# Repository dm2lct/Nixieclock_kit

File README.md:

Better version of my nixie clock. 
=====

Feel free to build your own nixie clock from it.

The firmware can be found at https://codeberg.org/paul/nixie_clock

The documentation and assembly instructions are on https://wiki.turmlabor.de/index.php?title=Nixie_Uhr_Bausatz_2.1 (currently only in german, sorry!)

Features:
  - IN14 nixie tubes but you can adapt many other nixie tubes, but some of them would not fit nicely in the board
  - ESP12e controller so you can make IoT with it and build your own botnet for world domination, if you have enough clocks.
    But mainly the wifi is used to get the time from a ntp-server and for controlling the clock with MQTT
  - DS3231 RTC for everyone who does not like IoT and does also not want to be enslaved from AI
  - WS2812B under each nixie tube to make them look more fancy
  - runs from a simple USB charger, although it uses a mini-usb B socket, which is better to solder, so you need a mini-usb cable
  - you can program the controller with your Arduino IDE over USB
  - optimized nixie power supply. Now the entire clock ownly draws about 450mA from the power supply
  - cleaned up the schematic a little: Simpler protection circuit

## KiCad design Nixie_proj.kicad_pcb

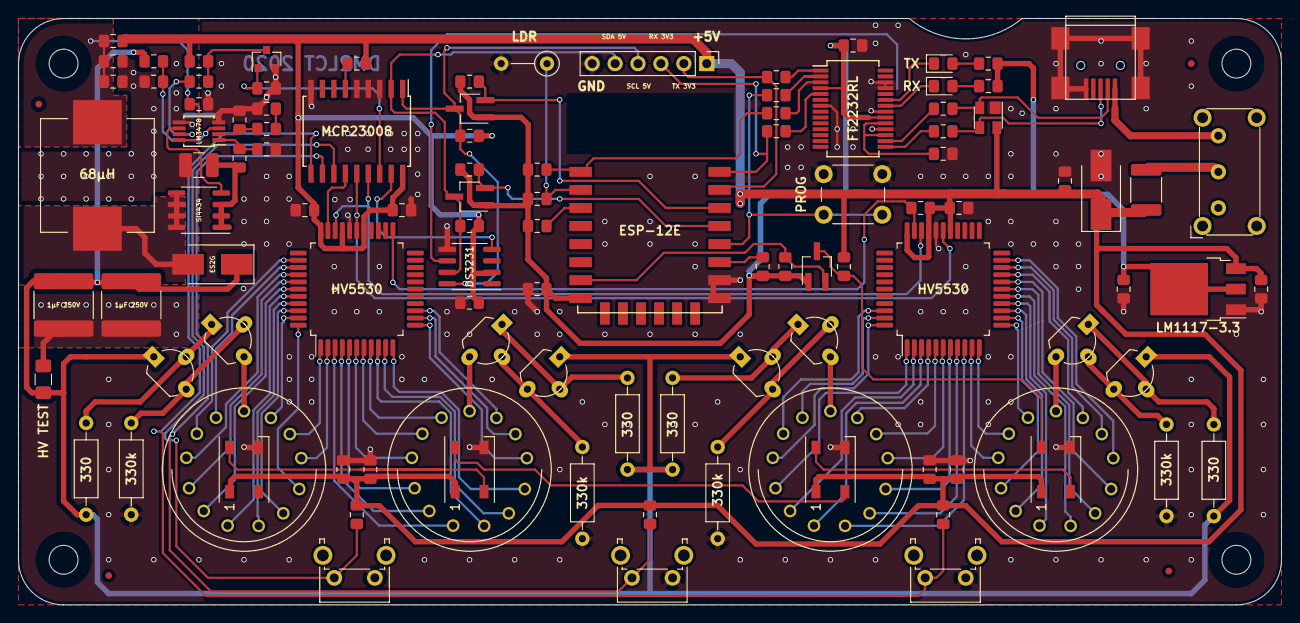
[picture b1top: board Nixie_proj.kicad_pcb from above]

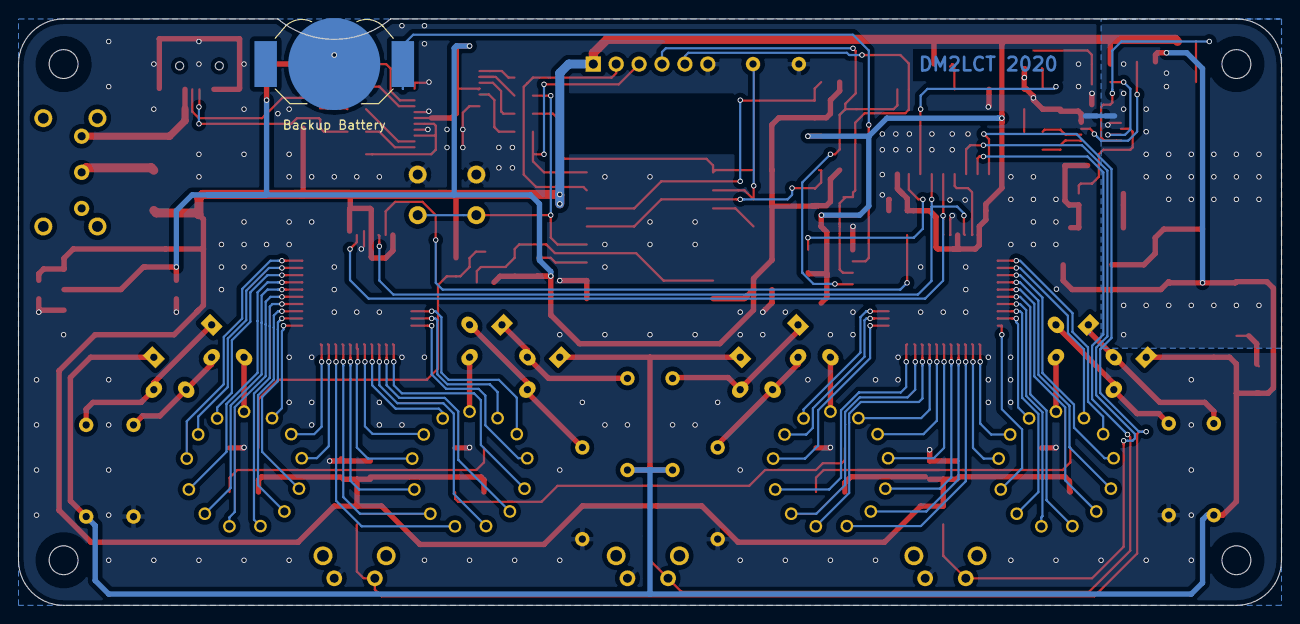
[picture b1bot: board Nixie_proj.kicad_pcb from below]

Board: 2 copper layers, 140.0 x 65.0 mm, 117 parts (2 on the bottom side), 117 nets.

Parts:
1µF 250V, 1µF 250V#2: 1u; C_2225_5664Metric_Pad1.80x6.60mm_HandSolder
68µH: INDUCTOR; L_Wuerth_WE-PD-Typ-LS_Handsoldering
330, 330#2, 330#3, 330#4: 330; R_Axial_DIN0207_L6.3mm_D2.5mm_P10.16mm_Horizontal
330k, 330k#2, 330k#3, 330k#4: 330k; R_Axial_DIN0207_L6.3mm_D2.5mm_P10.16mm_Horizontal
Backup Battery: Battery_Cell; BatteryHolder_LINX_BAT-HLD-012-SMT
C1, C5, C6, C8, C14, C16, C17, C18, C19, C20, C21, C22, C23, C201: 2.2u; C_0805_2012Metric_Pad1.15x1.40mm_HandSolder
C2, C3, C4: 22u; C_0805_2012Metric_Pad1.15x1.40mm_HandSolder
C7: 150p; C_0805_2012Metric_Pad1.15x1.40mm_HandSolder
C9: 1n; C_0805_2012Metric_Pad1.15x1.40mm_HandSolder
C305: 3n3; C_0805_2012Metric_Pad1.15x1.40mm_HandSolder
D1: P6SMB6,8A; D_SMB_Handsoldering
D2: PRTR5V0U2X; SOT-143
DS3231: DS3231MZ; SOIC-8_3.9x4.9mm_P1.27mm
ES2G: ES2G/SMB; D_SMB_Handsoldering
ESP-12E: ESP-12E; ESP-12E_SMD
F1: 2,2A; Fuse_1812_4532Metric_Pad1.30x3.40mm_HandSolder
FID1, FID2, FID3, FID4: Fiducial; Fiducial_0.75mm_Mask1.5mm
FT2232RL: FT232RL; SSOP-28_5.3x10.2mm_P0.65mm
H1, H2, H3: MountingHole; MountingHole_3.2mm_M3_DIN965
H4: eMountingHole; MountingHole_3.2mm_M3_DIN965
HV5530, HV5530#2: HV5530; MQFP-44_10x10mm_P0.8mm
HV TEST: TEST; R_1206_3216Metric_Pad1.42x1.75mm_HandSolder
J1: Conn_01x06_Male; PinHeader_1x06_P2.54mm_Vertical
L4: Ferrite_Bead; L_0805_2012Metric_Pad1.15x1.40mm_HandSolder
LDR: R_PHOTO; R_Axial_DIN0207_L6.3mm_D2.5mm_P5.08mm_Vertical
LED401, LED402, LED403, LED404: WS2812B; LED_WS2812B_PLCC4_5.0x5.0mm_P3.2mm
LM1117-3.3: LM1117-3.3; TO-252-3_TabPin2
LM3478: LM3478; MSOP-8_3x3mm_P0.65mm
MCP23008: MCP23008; SOIC-18W_7.5x11.6mm_P1.27mm
NT1: Net-Tie_2; NetTie-2_SMD_Pad0.5mm
P301: USB Buchse; USB_Mini-B
PROG: SW_Push; SW_PUSH_6mm_H4.3mm
Q2: BSS138; SOT-23
Q202, Q203, Q204, Q205, Q206, Q207, Q208, Q209: MPSA92; TO-92_Molded_Wide_Oval
Q401, Q403, Q404: BSS138; SOT-23W_Handsoldering
R1: 68k1; R_0805_2012Metric_Pad1.15x1.40mm_HandSolder
R2, R3, R206, R310, R401, R402, R403, R410, R411, R412, R413, R414, R416, R417, R418, R419, R420, R421: 10k; R_0805_2012Metric_Pad1.15x1.40mm_HandSolder
R4: 51k1; R_0805_2012Metric_Pad1.15x1.40mm_HandSolder
R5: 1k; R_0805_2012Metric_Pad1.15x1.40mm_HandSolder
R308: 1M5; R_0805_2012Metric_Pad1.15x1.40mm_HandSolder
R404, R405, R406, R407: 10R; R_0805_2012Metric_Pad1.15x1.40mm_HandSolder
R408, R409: 120; R_0805_2012Metric_Pad1.15x1.40mm_HandSolder
RSENSE301: 0R050; R_1210_3225Metric_Pad1.42x2.65mm_HandSolder
RX: GRÜN; LED_0805_2012Metric_Pad1.15x1.40mm_HandSolder
SI4434: SI4434; SOIC-8_3.9x4.9mm_P1.27mm
SW1: EG1224; SW_E-Switch_EG1224_SPDT_Angled
SW402: Rechts; SW_Tactile_SPST_Angled_PTS645Vx39-2LFS
SW403: Mitte; SW_Tactile_SPST_Angled_PTS645Vx39-2LFS
SW404: Links; SW_Tactile_SPST_Angled_PTS645Vx39-2LFS
TBE201, TBE202, TBE203, TBE204: IN14; IN-14-mod
TX: ROT; LED_0805_2012Metric_Pad1.15x1.40mm_HandSolder
W401, W402: TEST_2P; R_0805_2012Metric_Pad1.15x1.40mm_HandSolder

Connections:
+3V3: C6.1, C18.1, C21.2, ESP-12E.8, FT2232RL.4, FT2232RL.20, LM1117-3.3.2, Q401.1, Q403.1, Q404.1, R408.1, R409.1, R410.1, R412.1, R413.1, R414.1, R418.1, R419.1, R420.1
+5V: C1.1, C2.1, C5.1, C14.1, C16.1, C17.1, C20.1, C22.1, C23.2, C201.1, D1.1, D2.4, DS3231.2, F1.1, HV5530.27, HV5530.30, HV5530.33, HV5530#2.27, HV5530#2.30, HV5530#2.33, J1.1, L4.2, LED401.1, LED402.1, LED403.1, LED404.1, LM1117-3.3.3, MCP23008.18, R3.2, R206.1, R401.2, R402.2, R403.2, R411.1, R416.1, R417.1, R421.1
/Microcontroller and clock/BTN1: MCP23008.10, R401.1, SW402.2
/Microcontroller and clock/BTN2: MCP23008.11, R402.1, SW403.2
/Microcontroller and clock/BTN3: MCP23008.12, R403.1, SW404.2
/Microcontroller and clock/HVCLOCK: HV5530.28, HV5530#2.28, MCP23008.14
/Microcontroller and clock/HVDATA: HV5530.32, MCP23008.13
/Microcontroller and clock/HVSTROBE: HV5530.31, HV5530#2.31, MCP23008.15
/Microcontroller and clock/HV_SHDN: MCP23008.16, Q2.1, R2.2
/Microcontroller and clock/RX: ESP-12E.16, J1.3, R407.1
/Microcontroller and clock/SCL_3V3: ESP-12E.14, Q403.2, R413.2
/Microcontroller and clock/SCL_5V: DS3231.8, J1.4, MCP23008.1, Q403.3, R416.2
/Microcontroller and clock/SDA_3V3: ESP-12E.13, Q404.2, R412.2
/Microcontroller and clock/SDA_5V: DS3231.7, J1.5, MCP23008.2, Q404.3, R417.2
/Microcontroller and clock/TX: ESP-12E.15, J1.2, R406.1
/Microcontroller and clock/USBD+: D2.3, P301.3, R404.2
/Microcontroller and clock/USBD-: D2.2, P301.2, R405.2
/Power Supply/Boost_Drain: 68µH.2, ES2G.2, SI4434.5, SI4434.6, SI4434.7, SI4434.8
/Power Supply/Boost_ZK: 68µH.1, C3.1, C4.1, C8.2, L4.1, LM3478.8
/Power Supply/FB: LM3478.3, R308.2, R310.1
/Power Supply/Isen: C9.2, LM3478.1, R5.2
/Power Supply/PWRGND: 1µF 250V.2, 1µF 250V#2.2, C3.2, C4.2, HV TEST.2, LM3478.5, NT1.1, R310.2, RSENSE301.2
/Tubes with drivers/A0: HV5530.2, TBE201.11
/Tubes with drivers/A1: HV5530.35, TBE201.3
/Tubes with drivers/A2: HV5530.37, TBE201.4
/Tubes with drivers/A3: HV5530.38, TBE201.5
/Tubes with drivers/A4: HV5530.39, TBE201.6
/Tubes with drivers/A5: HV5530.40, TBE201.7
/Tubes with drivers/A6: HV5530.41, TBE201.8
/Tubes with drivers/A7: HV5530.42, TBE201.9
/Tubes with drivers/A8: HV5530.44, TBE201.10
/Tubes with drivers/A9: HV5530.1, TBE201.12
/Tubes with drivers/AC1: HV5530.36, TBE201.2
/Tubes with drivers/AC2: HV5530.43, TBE201.13
/Tubes with drivers/B0: HV5530.13, TBE202.12
/Tubes with drivers/B1: HV5530.5, TBE202.5
/Tubes with drivers/B2: HV5530.6, TBE202.4
/Tubes with drivers/B3: HV5530.7, TBE202.3
/Tubes with drivers/B4: HV5530.4, TBE202.6
/Tubes with drivers/B5: HV5530.3, TBE202.7
/Tubes with drivers/B6: HV5530.9, TBE202.8
/Tubes with drivers/B7: HV5530.10, TBE202.9
/Tubes with drivers/B8: HV5530.11, TBE202.10
/Tubes with drivers/B9: HV5530.12, TBE202.11
/Tubes with drivers/BC1: HV5530.8, TBE202.2
/Tubes with drivers/BC2: HV5530.14, TBE202.13
/Tubes with drivers/C0: HV5530#2.9, TBE203.8
/Tubes with drivers/C1: HV5530#2.42, TBE203.3
/Tubes with drivers/C2: HV5530#2.44, TBE203.4
/Tubes with drivers/C3: HV5530#2.1, TBE203.5
/Tubes with drivers/C4: HV5530#2.2, TBE203.6
/Tubes with drivers/C5: HV5530#2.3, TBE203.7
/Tubes with drivers/C6: HV5530#2.5, TBE203.12
/Tubes with drivers/C7: HV5530#2.6, TBE203.11
/Tubes with drivers/C8: HV5530#2.7, TBE203.10
/Tubes with drivers/C9: HV5530#2.8, TBE203.9
/Tubes with drivers/CC1: HV5530#2.43, TBE203.2
/Tubes with drivers/CC2: HV5530#2.4, TBE203.13
/Tubes with drivers/D0: HV5530#2.20, TBE204.12
/Tubes with drivers/D1: HV5530#2.11, TBE204.3
/Tubes with drivers/D2: HV5530#2.10, TBE204.4
/Tubes with drivers/D3: HV5530#2.13, TBE204.5
/Tubes with drivers/D4: HV5530#2.14, TBE204.6
/Tubes with drivers/D5: HV5530#2.15, TBE204.7
/Tubes with drivers/D6: HV5530#2.16, TBE204.8
/Tubes with drivers/D7: HV5530#2.17, TBE204.9
/Tubes with drivers/D8: HV5530#2.18, TBE204.10
/Tubes with drivers/D9: HV5530#2.21, TBE204.11
/Tubes with drivers/DC1: HV5530#2.12, TBE204.2
/Tubes with drivers/DC2: HV5530#2.19, TBE204.13
GND: 330k.2, 330k#2.2, 330k#3.2, 330k#4.2, Backup Battery.2, C1.2, C2.2, C5.2, C6.2, C7.2, C8.1, C9.1, C14.2, C16.2, C17.2, C18.2, C19.2, C20.2, C21.1, C22.2, C23.1, C201.2, D1.2, D2.1, DS3231.5, ESP-12E.9, ESP-12E.10, FT2232RL.7, FT2232RL.18, FT2232RL.21, FT2232RL.25, FT2232RL.26, HV5530.29, HV5530#2.29, J1.6, LDR.2, LED401.3, LED402.3, LED403.3, LED404.3, LM1117-3.3.1, LM3478.4, MCP23008.3, MCP23008.4, MCP23008.5, MCP23008.9, NT1.2, P301.5, P301.6, PROG.2, Q2.2, R1.2, R2.1, SW402.1, SW403.1, SW404.1
unnamed: Backup Battery.1, DS3231.6
unnamed: C19.1, FT2232RL.17, FT2232RL.19
unnamed: C7.1, C305.1, LM3478.2
unnamed: C305.2, R1.1
unnamed: FT2232RL.23, TX.1
unnamed: R408.2, TX.2
unnamed: FT2232RL.22, RX.1
unnamed: R409.2, RX.2
unnamed: F1.2, SW1.2
unnamed: LED401.4, LED402.2
unnamed: LED402.4, LED403.2
unnamed: LED403.4, LED404.2
unnamed: LED404.4, Q401.3, R411.2
unnamed: P301.1, SW1.3
unnamed: R5.1, RSENSE301.1, SI4434.1, SI4434.2, SI4434.3
unnamed: LM3478.6, SI4434.4
unnamed: Q2.3, R3.1, R4.2
unnamed: 330.2, Q202.2, Q203.1
unnamed: 330k.1, Q202.3, Q203.2
unnamed: Q203.3, TBE201.1
unnamed: 330#2.2, Q204.2, Q205.1
unnamed: 330k#2.1, Q204.3, Q205.2
unnamed: Q205.3, TBE202.1
unnamed: 330#3.2, Q206.2, Q207.1
unnamed: 330k#3.1, Q206.3, Q207.2
unnamed: Q207.3, TBE203.1
unnamed: 330#4.2, Q208.2, Q209.1
unnamed: 330k#4.1, Q208.3, Q209.2
unnamed: Q209.3, TBE204.1
unnamed: ESP-12E.7, Q401.2, R410.2
unnamed: LM3478.7, R4.1
unnamed: HV5530.23, HV5530#2.32, R206.2
unnamed: FT2232RL.15, R404.1
unnamed: FT2232RL.16, R405.1
unnamed: FT2232RL.1, R406.2
unnamed: FT2232RL.5, R407.2
unnamed: ESP-12E.2, LDR.1, R414.2
unnamed: ESP-12E.3, R418.2
unnamed: ESP-12E.1, R419.2, W401.2
unnamed: ESP-12E.11, R420.2
unnamed: MCP23008.6, R421.2
unnamed: ESP-12E.12, PROG.1, W402.2
unnamed: DS3231.4, MCP23008.17
unnamed: FT2232RL.2, W402.1
unnamed: FT2232RL.3, W401.1
VAA: 1µF 250V.1, 1µF 250V#2.1, 330.1, 330#2.1, 330#3.1, 330#4.1, ES2G.1, HV TEST.1, Q202.1, Q204.1, Q206.1, Q208.1, R308.1

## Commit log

2020-12-30 neues repo aufgemacht, das alte war kaputtgespielt...
2020-12-30 Kleinigkeiten
2020-12-30 nettes foto gemacht...
2020-12-30 wenn man einmal anfängt...
2021-01-19 Fertigungsdaten erstellt
2021-03-26 bom hinzugefügt
2021-03-26 mal wieder aktualisiert
